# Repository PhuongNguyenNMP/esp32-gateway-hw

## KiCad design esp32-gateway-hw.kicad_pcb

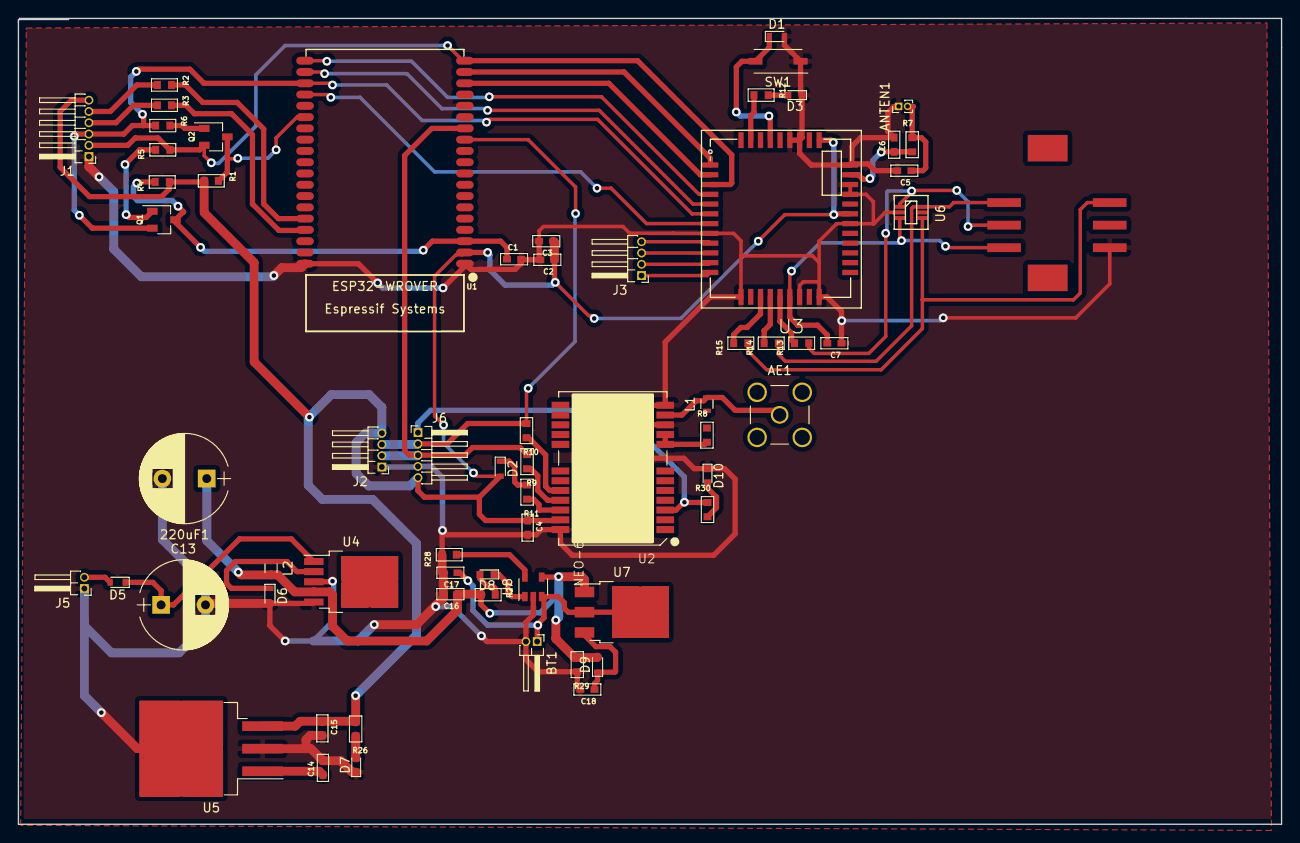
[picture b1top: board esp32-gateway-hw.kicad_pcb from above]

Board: 2 copper layers, 142.2 x 90.7 mm, 65 parts (0 on the bottom side), 55 nets.

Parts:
220uF1: CP; CP_Radial_D10.0mm_P5.00mm
AE1: Antenna; SMA_Straight
ANTEN1: LEMO2; Pin_Header_Straight_1x02_Pitch1.00mm
BT1: Battery; Pin_Header_Angled_1x02_Pitch1.27mm
C1: 0.1uF/50V; C_0603
C2: 0.1uF; C_0603
C3, C4: 10uF; C_0603
C5, C6, C7: C; C_0603
C13: 680uF; CP_Radial_D10.0mm_P5.00mm
C14, C15, C18: 1uF; C_0603
C16, C17: 4.7uF; C_0603
D1: D_TVS; D_0603
D2: 1N4148; D_0603
D3, D7, D8, D10: LED; LED_0603
D5, D6, D9: D_Schottky_Small; D_0603
J1: Conn_01x06; Pin_Header_Angled_1x06_Pitch1.27mm
J2, J3: Conn_01x04; Pin_Header_Angled_1x04_Pitch1.27mm
J4: SIM_Card; simcard
J5: Conn_01x02; Pin_Header_Angled_1x02_Pitch1.27mm
J6: Conn_01x05; Pin_Header_Angled_1x05_Pitch1.27mm
L1: 22uH; L_0603
L2: 33uH; L_0603
Q1, Q2: 2SC1945; SOT-23_standar
R1: 10k/1%; R_0603
R2, R3, R5, R6, R26, R27: 470R; R_0603
R4: 10k; R_0603
R7, R30: R; R_0603
R8: 220; R_0603
R9, R10: 10; R_0603
R11: 120; R_0603
R12: 330; R_0603
R13, R14, R15: 100; R_0603
R28: 10K; R_0603
R29: 100K; R_0603
SW1: SW_Push; SW_DIP_x1_W5.08mm_Slide_Copal_CHS-A
U1: ESP32-WROVER-V3; esp32-wrover-32S
U2: NEO-6M; GPS24P-SMD-1.1-16X12.2MM
U3: SIM800C-RESCUE-esp32-gateway-hw; sim800c
U4: LM2596; TO-252-5_TabPin6
U5: TC1264; TO-263-3_TabPin2
U6: SP1001
U7: MOSFET-P; TO-252-3_TabPin2
U8: MCP73831-2-OT; SOT-23-5

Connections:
+3V3: C2.1, C3.1, C4.1, C15.1, D2.2, J1.6, J2.4, J6.5, R1.1, R4.1, R26.1, U1.2, U2.23, U3.28, U3.34, U3.35, U5.3
+5VD: 220uF1.1, C16.1, D9.2, L2.2, R27.1, R29.1, U4.4, U7.1, U8.4
CTS: U1.20, U3.4
DCD: U1.21, U3.5
DTR: J1.3, Q1.2, R6.1, U1.22, U3.6
EN: C1.1, Q1.3, R4.2, U1.3
GND: 220uF1.2, ANTEN1.1, BT1.2, C1.2, C2.2, C3.2, C4.2, C5.2, C6.2, C7.1, C13.2, C14.2, C15.2, C16.2, C17.2, C18.2, D1.2, D3.1, D6.2, D7.1, D10.1, J1.1, J2.1, J4.4, J5.1, J6.4, R28.2, R29.2, SW1.1, U1.1, U1.15, U1.38, U2.10, U2.12, U2.24, U3.8, U3.13, U3.19, U3.21, U3.27, U3.30, U3.31, U3.33, U3.36, U3.37, U4.3, U4.5, U5.2, U6.2, U8.2
IO0: Q2.3, R1.2, U1.25
unnamed: AE1.1, L1.2, U2.11
unnamed: ANTEN1.2, C5.1, R7.2
unnamed: BT1.1, C17.1, U7.2, U8.3
unnamed: C6.1, R7.1, U3.32
unnamed: C7.2, J4.1, U3.18, U6.3
unnamed: C13.1, D5.1, U4.1
unnamed: C14.1, U5.1
unnamed: C18.1, D9.1, U7.3
unnamed: D1.1, SW1.2, U3.39
unnamed: D2.1, R11.1
unnamed: D3.2, R12.2
unnamed: D5.2, J5.2
unnamed: D6.1, L2.1, U4.2
unnamed: D7.2, R26.2
unnamed: D8.1, U8.1
unnamed: D8.2, R27.2
unnamed: D10.2, R30.1
unnamed: J1.4, R3.1
unnamed: J1.5, R2.1
unnamed: J3.1, U3.12
unnamed: J3.2, U3.11
unnamed: J3.3, U3.10
unnamed: J3.4, U3.9
unnamed: J4.2, R13.1, U6.1
unnamed: J4.3, R14.1, U6.6
unnamed: J4.6, R15.1, U6.4
unnamed: L1.1, R8.2
unnamed: Q1.1, R5.2
unnamed: Q2.1, R6.2
unnamed: R8.1, U2.8, U2.9
unnamed: R9.2, U2.21
unnamed: R10.2, U2.20
unnamed: R11.2, U2.22
unnamed: R12.1, U3.41
unnamed: R13.2, U3.17
unnamed: R14.2, U3.16
unnamed: R15.2, U3.15
unnamed: R28.1, U8.5
PULSE: J6.1, R30.2, U2.3
RI: U1.23, U3.7
RTS: J1.2, Q2.2, R5.1, U1.19, U3.3
RXD: R2.2, U1.34
RXD-01: U1.17, U3.2
RXD-02: J2.3, J6.2, R10.1, U1.12
TXD: R3.2, U1.35
TXD-01: U1.18, U3.1
TXD-02: J2.2, J6.3, R9.1, U1.13

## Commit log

2017-10-11 add layout
2017-10-11 bigfix connect GND
